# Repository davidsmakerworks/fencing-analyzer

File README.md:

# fencing-analyzer
Wireless fencing action analyzer

This is a KiCad project and MPLAB X project for a wireless intertial module, which is eventually planned to be used for analysis of actions by fencers. This uses the lsm6ds3x driver from the [drivers](https://github.com/davidsmakerworks/drivers) repository.

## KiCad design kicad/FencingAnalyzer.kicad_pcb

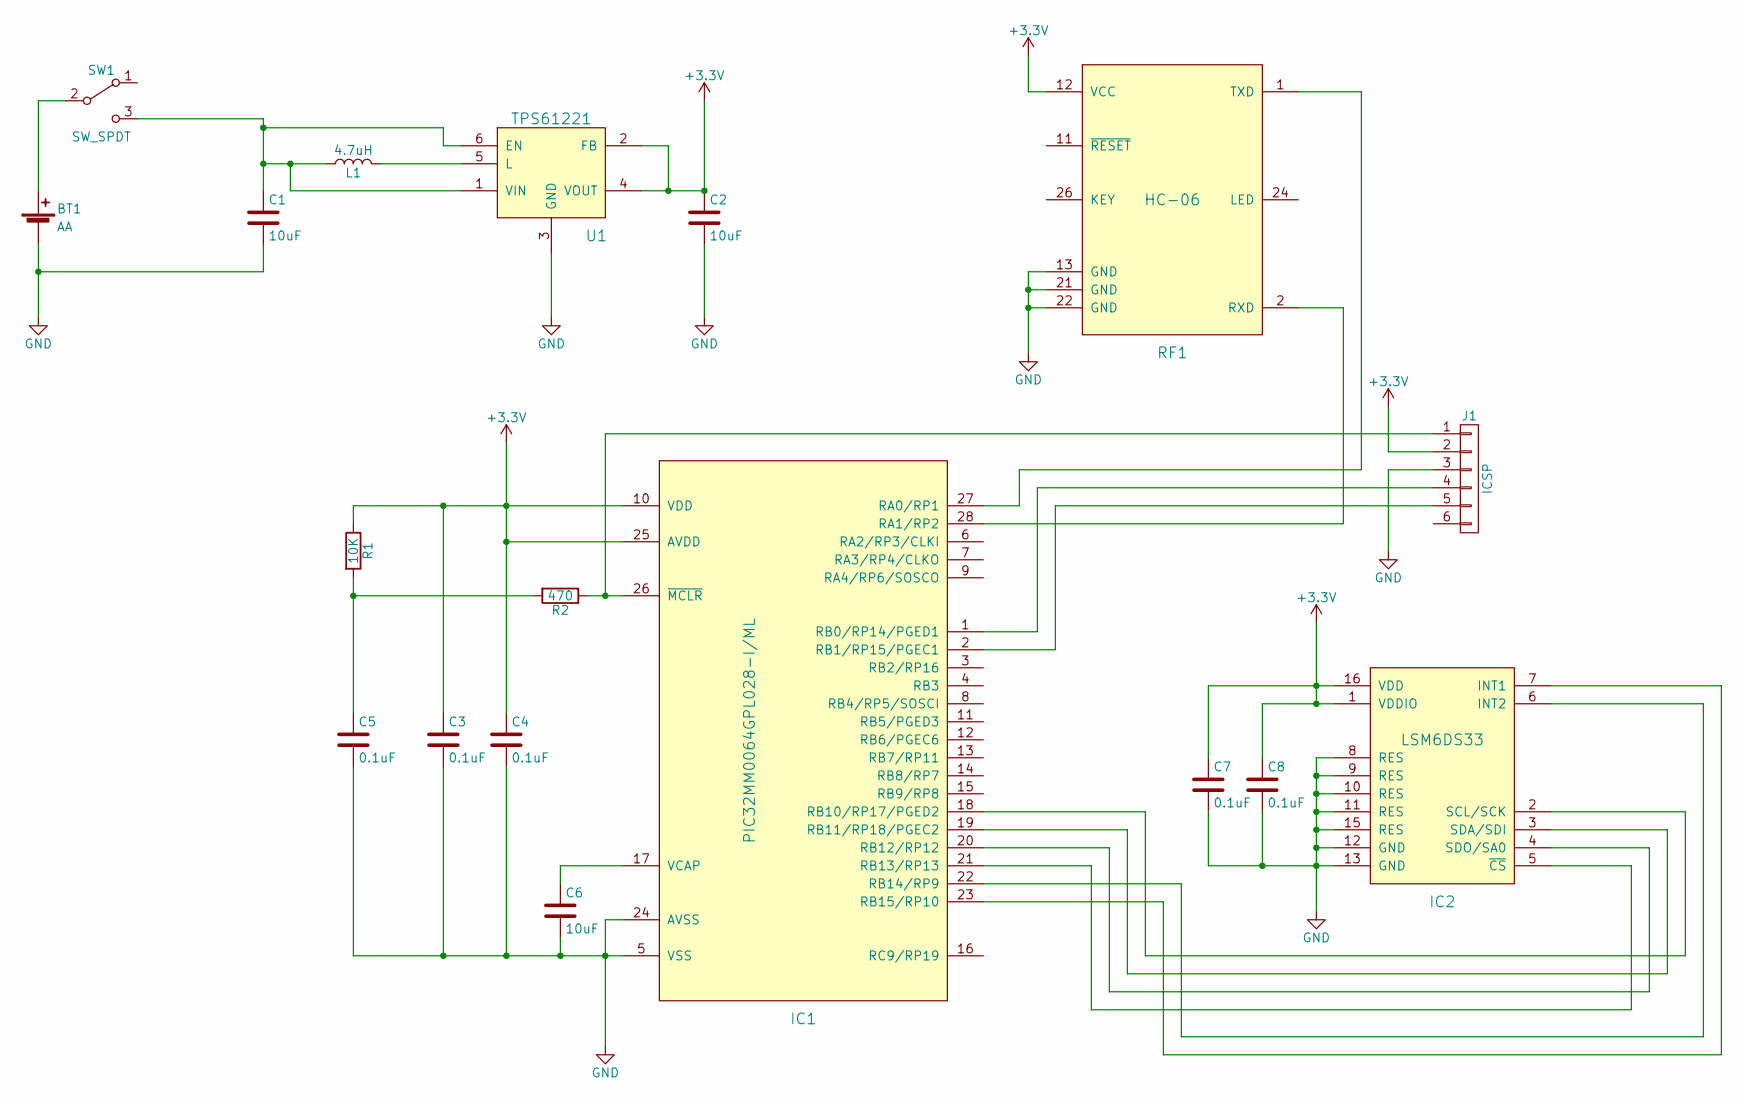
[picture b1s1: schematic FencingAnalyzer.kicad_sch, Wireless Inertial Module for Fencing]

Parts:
BT1: AA; Pin_Header_Straight_1x02_Pitch2.54mm
C1, C2, C6: 10uF; C_0805
C3, C4, C5, C7, C8: 0.1uF; C_0603
IC1: PIC32MM0064GPL028-I/ML; QFN-28-1EP_6x6mm_Pitch0.65mm
IC2: LSM6DS33; LGA-16-3x3
J1: ICSP; Pin_Header_Straight_1x06_Pitch2.54mm
L1: 4.7uH; LQH3NP
R1: 10K; R_0805
R2: 470; R_0805
RF1: HC-06; HC-06_SMD_Module
SW1: SW_SPDT; 6-pin_SMD_Switch
U1: TPS61221; SOT-363_SC-70-6

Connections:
+3V3: C2.1, C3.1, C4.1, C7.1, C8.1, IC1.10 (VDD), IC1.25 (AVDD), IC2.1 (VDDIO), IC2.16 (VDD), J1.2, R1.1, RF1.12 (VCC), U1.2 (FB), U1.4 (VOUT); also elsewhere on the board
GND: BT1.2 (-), C1.2, C2.2, C3.2, C4.2, C5.2, C6.2, C7.2, C8.2, IC1.5 (VSS), IC1.24 (AVSS), IC1.29, IC2.8 (RES), IC2.9 (RES), IC2.10 (RES), IC2.11 (RES), IC2.12 (GND), IC2.13 (GND), IC2.15 (RES), J1.3, RF1.13 (GND), RF1.21 (GND), RF1.22 (GND), U1.3 (GND); also elsewhere on the board
unnamed: BT1.1 (+), SW1.2 (B)
unnamed: C1.1, L1.1, SW1.3 (C), U1.1 (VIN), U1.6 (EN)
unnamed: C5.1, R1.2, R2.2
unnamed: C6.1, IC1.17 (VCAP)
unnamed 6: IC1.1 (RB0/RP14/PGED1), J1.4; also elsewhere on the board
unnamed 7: IC1.2 (RB1/RP15/PGEC1), J1.5; also elsewhere on the board
unnamed: IC1.18 (RB10/RP17/PGED2), IC2.2 (SCL/SCK)
unnamed: IC1.19 (RB11/RP18/PGEC2), IC2.3 (SDA/SDI)
unnamed: IC1.20 (RB12/RP12), IC2.4 (SDO/SA0)
unnamed: IC1.21 (RB13/RP13), IC2.5 (~CS)
unnamed: IC1.22 (RB14/RP9), IC2.6 (INT2)
unnamed: IC1.23 (RB15/RP10), IC2.7 (INT1)
unnamed 26: IC1.26 (~MCLR), J1.1, R2.1; also elsewhere on the board
unnamed: IC1.27 (RA0/RP1), RF1.1 (TXD)
unnamed: IC1.28 (RA1/RP2), RF1.2 (RXD)
unnamed: L1.2, U1.5 (L)

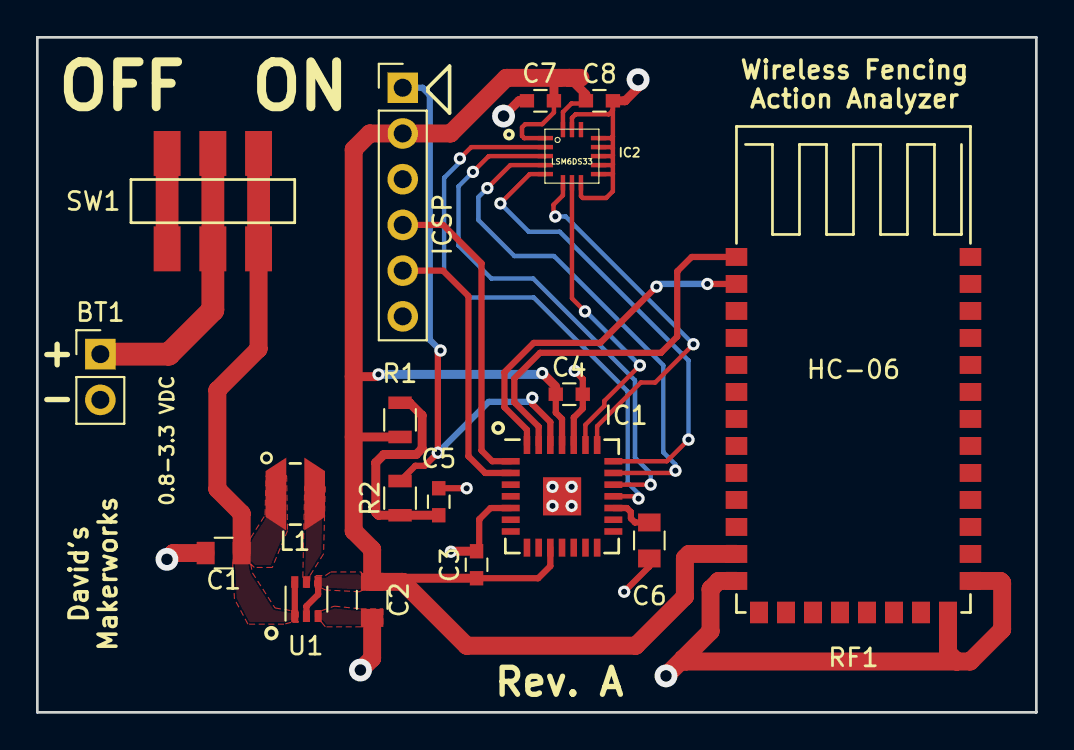
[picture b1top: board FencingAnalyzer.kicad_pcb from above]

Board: 2 copper layers, 55.5 x 37.5 mm, 18 parts (0 on the bottom side), 18 nets.

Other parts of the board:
ICSP: ICSP; Pin_Header_Straight_1x06_Pitch2.54mm

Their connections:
+3V3: ICSP.2; also elsewhere on the board
GND: ICSP.3; also elsewhere on the board
unnamed 6: ICSP.4; also elsewhere on the board
unnamed 7: ICSP.5; also elsewhere on the board
unnamed 26: ICSP.1; also elsewhere on the board

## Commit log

2019-06-23 Create LICENSE
2019-06-23 Point to new drivers location
2019-06-24 Update library locations
2020-11-20 Update gitignore, update compiler and pack versions
2020-12-07 Remove unnecessary files
2020-12-25 Refactor code structure for reusability
2023-03-18 Update text on silkscreen and in user interface, update for KiCad 7
